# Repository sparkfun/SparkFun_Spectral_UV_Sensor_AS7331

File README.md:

SparkFun Spectral UV Sensor - AS7331 (Qwiic) 
========================================

<table class="table table-hover table-striped table-bordered">
    <tr align="center">
        <td></td>
        <td></td>
    </tr>
    <tr align="center">
        <td><a href="https://www.sparkfun.com/products/23517">SparkFun Spectral UV Sensor - AS7331 (Qwiic)</a></td>
        <td><a href="https://www.sparkfun.com/products/23518">SparkFun Mini Spectral UV Sensor - AS7331 (Qwiic)</a></td>
    </tr>
</table>

The SparkFun Spectral UV Sensor - AS7331 (Qwiic) features the AS7331 UV sensor from ams OSRAM<sup>&copy;</sup> and measures UV radiation on three channels: UVA (320-400nm), UVB (280-320nm), and UVC (200-280nm) with high sensitivity and accuracy. The three channels on the AS7331 each have individual photodiodes with built-in interference filters. The sensor has three operating modes: Single Measurement (CMD), Continuous Measurement (CONT), and Synchronized Measurement (SYNx) with an automatic power down sequence between measurements for low current consumption in all three modes. 

Repository Contents
-------------------

* **/Documentation** - Data sheets, additional product information
* **/Hardware** - Eagle design files (.brd, .sch)
* **/Production** - Production panel files (.brd)
* **/docs** -  Documentation files for the Spectral UV Sensor
* **/overrides** -  Overrides for GitHub pages content

Documentation
--------------
* **[Library](https://github.com/sparkfun/SparkFun_AS7331_Arduino_Library)** - Arduino library for the Spectral UV Sensor - AS7331 (Qwiic).
* **[Hookup Guide](https://sparkfun.github.io/SparkFun_Spectral_UV_Sensor_AS7331)** - Basic hookup guide for the Spectral UV Sensor - AS7331 (Qwiic).

Product Versions
----------------
* [SEN-23517](https://www.sparkfun.com/products/23517) - Spectral UV Sensor - AS7331 (Qwiic)
* [SEN-23518](https://www.sparkfun.com/products/23518) - Mini Spectral UV Sensor - AS7331 (Qwiic)

License Information
-------------------

This product is _**open source**_! 

Please review the LICENSE.md file for license information. 

If you have any questions or concerns on licensing, please contact technical support on our [SparkFun forums](https://forum.sparkfun.com/viewforum.php?f=152).

Distributed as-is; no warranty is given.

- Your friends at SparkFun.

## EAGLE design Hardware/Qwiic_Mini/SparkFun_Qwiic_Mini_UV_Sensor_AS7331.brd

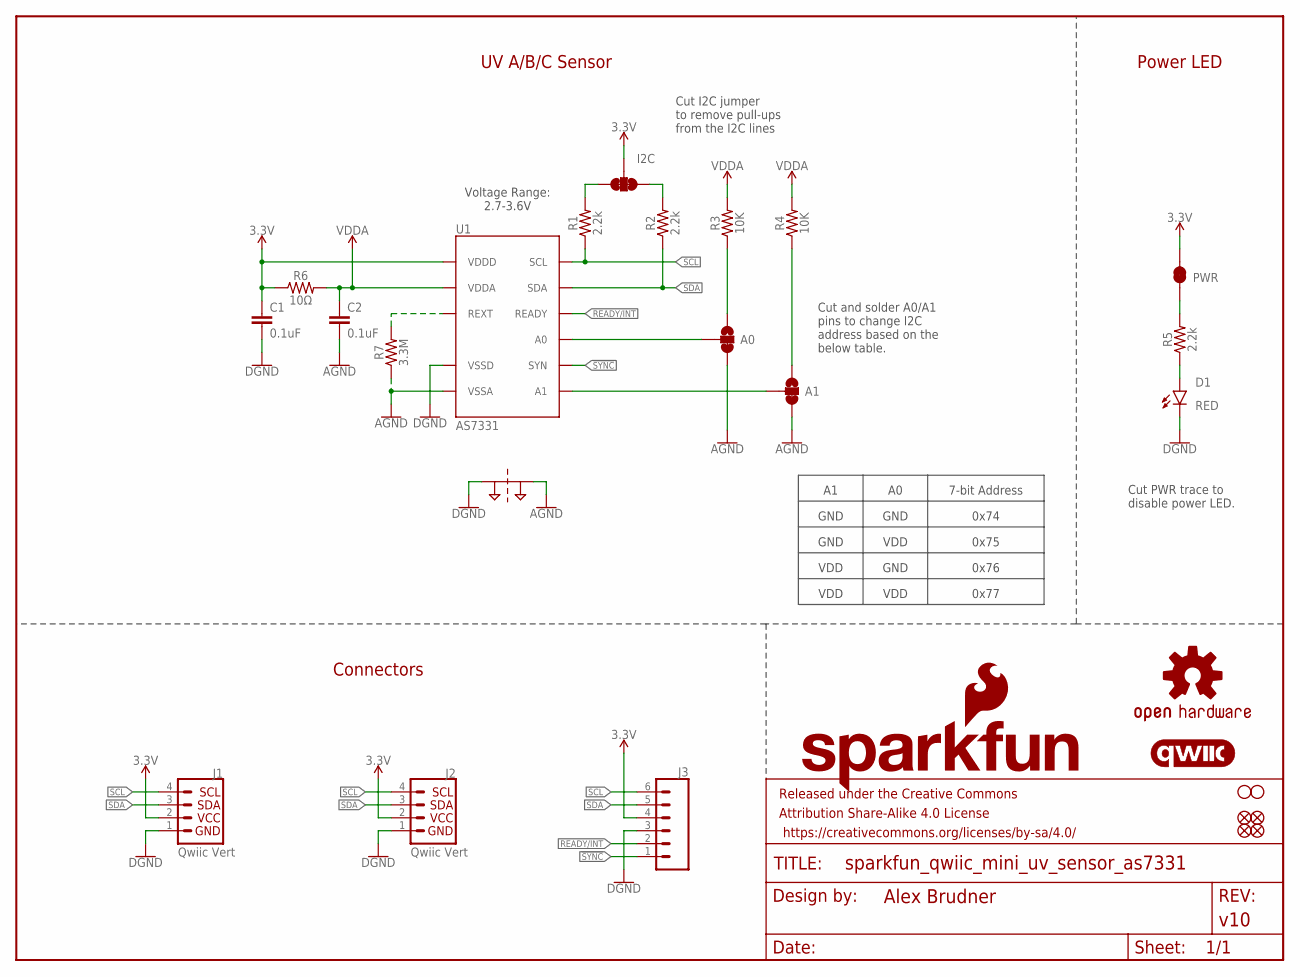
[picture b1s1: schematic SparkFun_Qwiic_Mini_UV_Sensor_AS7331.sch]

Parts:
A0, A1: JUMPER-SMT_3_1-NC_TRACE_SILK; SMT-JUMPER_3_1-NC_TRACE_SILK
C1, C2: 0.1uF; 0402-TIGHT
D1: RED; LED-0402
FD1, FD2, FD3, FD4: FIDUCIALUFIDUCIAL; FIDUCIAL-MICRO
FRAME1: FRAME-LETTER; CREATIVE_COMMONS
H1, H2: STAND-OFFTIGHT; STAND-OFF-TIGHT
I2C: JUMPER-SMT_3_2-NC_TRACE_SILK; SMT-JUMPER_3_2-NC_TRACE_SILK
J1, J2: Qwiic Vert; JST04_1MM_VERT
J3: CONN_06NO_SILK_NO_POP; 1X06_NO_SILK
LOGO1: SFE_LOGO_NAME.1_INCH; SFE_LOGO_NAME_.1
LOGO2: QWIIC_LOGO_CONNECTOR; QWIIC_5.5MM
LOGO3: OSHW-LOGOMINI; OSHW-LOGO-MINI
LOGO4: SFE_LOGO_FLAME.1_INCH; SFE_LOGO_FLAME_.1
PWR: JUMPER-SMT_2_NC_TRACE_SILK; SMT-JUMPER_2_NC_TRACE_SILK
R1, R2, R5: 2.2k; 0402-TIGHT
R3, R4: 10K; 0402-TIGHT
R6: 10Ω; 0402-TIGHT
R7: 3.3M; 1206
SUPPLYTIE1: 2PT_GND_TIE
U1: AS7331; OLGA16

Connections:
3.3V: C1.1, I2C.2, J1.2, J2.2, J3.4, PWR.2, R6.1, U1.10 (VDDD)
!SYNC: J3.1, U1.8 (SYN)
A0: A0.2, U1.14 (A0)
A1: A1.2, U1.7 (A1)
AGND: A0.3, A1.3, C2.2, R7.1, SUPPLYTIE1.P$2, U1.1 (VSSA), U1.2 (VSSA), U1.5 (VSSA), U1.6 (VSSA), U1.15 (VSSA), U1.16 (VSSA)
GND: C1.2, D1.C, J1.1, J2.1, J3.3, SUPPLYTIE1.P$1, U1.11 (VSSD)
unnamed: A0.1, R3.1
unnamed: A1.1, R4.1
unnamed: I2C.3, R1.2
unnamed: I2C.1, R2.2
unnamed: PWR.1, R5.2
unnamed: R7.2, U1.4 (REXT)
unnamed: D1.A, R5.1
READY/INT: J3.2, U1.9 (READY)
SCL: J1.4, J2.4, J3.6, R1.1, U1.13 (SCL)
SDA: J1.3, J2.3, J3.5, R2.1, U1.12 (SDA)
VDDA: C2.1, R3.2, R4.2, R6.2, U1.3 (VDDA)

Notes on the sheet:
Cut PWR trace to disable power LED.
Cut and solder A0/A1 pins to change I2C address based on the below table.
7-bit Address
GND
VDD
0x74
0x75
0x76
0x77
Connectors
UV A/B/C Sensor
Power LED
Cut I2C jumper to remove pull-ups from the I2C lines
Voltage Range: 2.7-3.6V

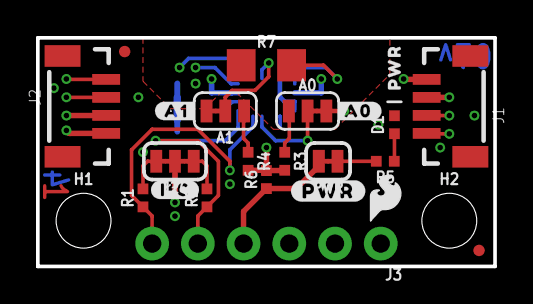
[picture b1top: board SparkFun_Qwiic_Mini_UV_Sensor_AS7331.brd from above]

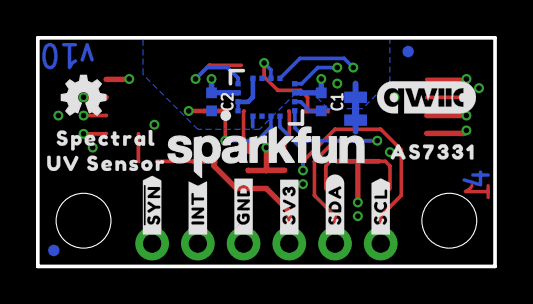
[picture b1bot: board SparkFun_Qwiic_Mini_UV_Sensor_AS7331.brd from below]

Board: 4 copper layers, 25.4 x 12.7 mm, 45 parts (18 on the bottom side), 17 nets.

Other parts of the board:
U$6: #I�C#0
U$7: #A0#0
U$8: #A1#0
U$9: #PWR#0
U$10: PWR0
U$11: #_SCL#0
U$12: #_SDA#0
U$13: #_3V3#0
U$14: #_GND#0
U$15: #_INT#0
U$17: UV_SENSOR0
U$18: AS73310
U$19: ORDERING_INSTRUCTIONS
U$20: SPECTRAL0
U$21: #_#SYN##0

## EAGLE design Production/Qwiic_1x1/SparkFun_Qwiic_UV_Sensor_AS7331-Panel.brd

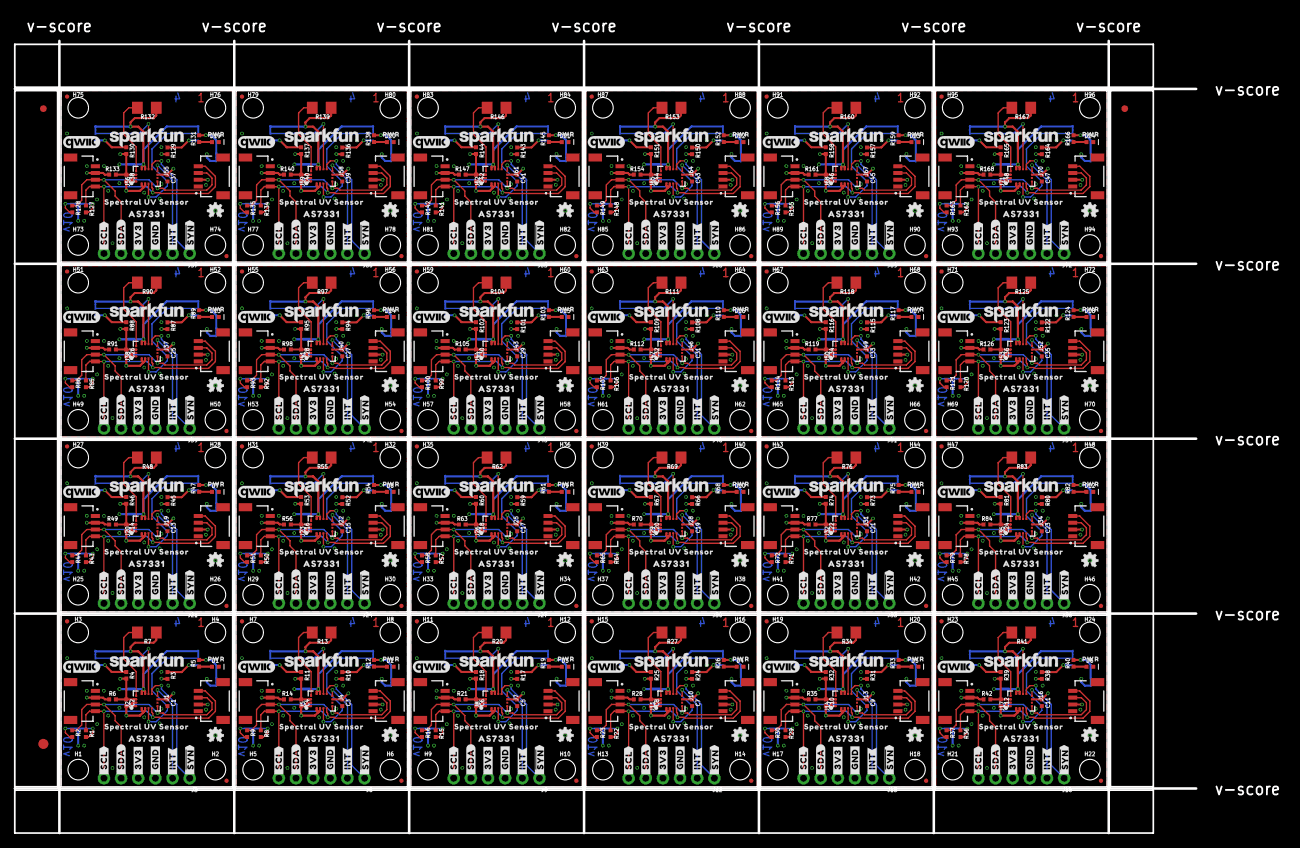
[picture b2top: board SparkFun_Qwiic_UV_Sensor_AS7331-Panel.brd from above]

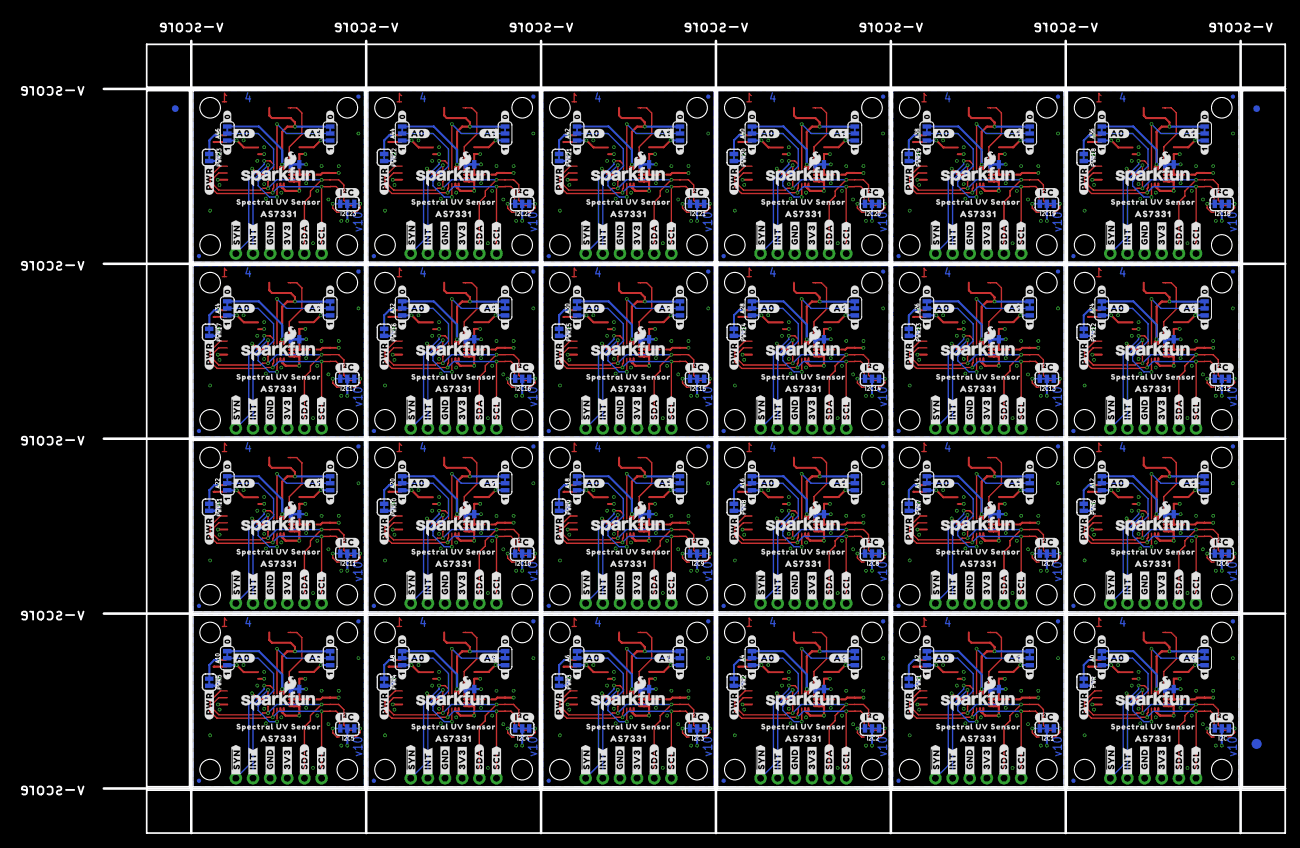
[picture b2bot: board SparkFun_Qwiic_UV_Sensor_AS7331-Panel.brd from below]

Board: 4 copper layers, 175.0 x 117.3 mm, 1374 parts (579 on the bottom side), 408 nets.

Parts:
A0, A1, A2, A3, A4, A5, A6, A7, A8, A9, A10, A11, A12, A13, A14, A15, A16, A17, A18, A19, A20, A21, A22, A23, A24, A25, A26, A27, A28, A29, A30, A31, A32, A33, A34, A35, A36, A37, A38, A39, A40, A41, A42, A43, A44, A45, A46, A47: JUMPER-SMT_3_1-NC_TRACE_SILK; SMT-JUMPER_3_1-NC_TRACE_SILK
C1, C2, C3, C4, C5, C6, C7, C8, C9, C10, C11, C12, C13, C14, C15, C16, C17, C18, C19, C20, C21, C22, C23, C24, C25, C26, C27, C28, C29, C30, C31, C32, C33, C34, C35, C36, C37, C38, C39, C40, C41, C42, C43, C44, C45, C46, C47, C48: 0.1uF; 0402-TIGHT
D1, D2, D3, D4, D5, D6, D7, D8, D9, D10, D11, D12, D13, D14, D15, D16, D17, D18, D19, D20, D21, D22, D23, D24: RED; LED-0402
E$1, E$2, E$3, E$4: FIDUCIAL-1X2
E$5, E$6: FIDUCIAL-1.5X3
FD1, FD2, FD3, FD4, FD5, FD6, FD7, FD8, FD9, FD10, FD11, FD12, FD13, FD14, FD15, FD16, FD17, FD18, FD19, FD20, FD21, FD22, FD23, FD24, FD25, FD26, FD27, FD28, FD29, FD30, FD31, FD32, FD33, FD34, FD35, FD36, FD37, FD38, FD39, FD40, FD41, FD42, FD43, FD44, FD45, FD46, FD47, FD48, FD49, FD50, FD51, FD52, FD53, FD54, FD55, FD56, FD57, FD58, FD59, FD60, FD61, FD62, FD63, FD64, FD65, FD66, FD67, FD68, FD69, FD70, FD71, FD72, FD73, FD74, FD75, FD76, FD77, FD78, FD79, FD80, FD81, FD82, FD83, FD84, FD85, FD86, FD87, FD88, FD89, FD90, FD91, FD92, FD93, FD94, FD95, FD96: FIDUCIALUFIDUCIAL; FIDUCIAL-MICRO
H1, H2, H3, H4, H5, H6, H7, H8, H9, H10, H11, H12, H13, H14, H15, H16, H17, H18, H19, H20, H21, H22, H23, H24, H25, H26, H27, H28, H29, H30, H31, H32, H33, H34, H35, H36, H37, H38, H39, H40, H41, H42, H43, H44, H45, H46, H47, H48, H49, H50, H51, H52, H53, H54, H55, H56, H57, H58, H59, H60, H61, H62, H63, H64, H65, H66, H67, H68, H69, H70, H71, H72, H73, H74, H75, H76, H77, H78, H79, H80, H81, H82, H83, H84, H85, H86, H87, H88, H89, H90, H91, H92, H93, H94, H95, H96: STAND-OFFTIGHT; STAND-OFF-TIGHT
I2C, I2C1, I2C2, I2C3, I2C4, I2C5, I2C6, I2C7, I2C8, I2C9, I2C10, I2C11, I2C12, I2C13, I2C14, I2C15, I2C16, I2C17, I2C18, I2C19, I2C20, I2C21, I2C22, I2C23: JUMPER-SMT_3_2-NC_TRACE_SILK; SMT-JUMPER_3_2-NC_TRACE_SILK
J1, J2, J4, J5, J7, J8, J10, J11, J13, J14, J16, J17, J19, J20, J22, J23, J25, J26, J28, J29, J31, J32, J34, J35, J37, J38, J40, J41, J43, J44, J46, J47, J49, J50, J52, J53, J55, J56, J58, J59, J61, J62, J64, J65, J67, J68, J70, J71: QWIIC_RA; JST04_1MM_RA
J3, J6, J9, J12, J15, J18, J21, J24, J27, J30, J33, J36, J39, J42, J45, J48, J51, J54, J57, J60, J63, J66, J69, J72: 1X06_NO_SILK
LOGO1, LOGO4, LOGO7, LOGO10, LOGO13, LOGO16, LOGO19, LOGO22, LOGO25, LOGO28, LOGO31, LOGO34, LOGO37, LOGO40, LOGO43, LOGO46, LOGO49, LOGO52, LOGO55, LOGO58, LOGO61, LOGO64, LOGO67, LOGO70: SFE_LOGO_NAME_FLAME.1_INCH; SFE_LOGO_NAME_FLAME_.1
LOGO2, LOGO5, LOGO8, LOGO11, LOGO14, LOGO17, LOGO20, LOGO23, LOGO26, LOGO29, LOGO32, LOGO35, LOGO38, LOGO41, LOGO44, LOGO47, LOGO50, LOGO53, LOGO56, LOGO59, LOGO62, LOGO65, LOGO68, LOGO71: QWIIC_LOGO_CONNECTOR; QWIIC_5.5MM
LOGO3, LOGO6, LOGO9, LOGO12, LOGO15, LOGO18, LOGO21, LOGO24, LOGO27, LOGO30, LOGO33, LOGO36, LOGO39, LOGO42, LOGO45, LOGO48, LOGO51, LOGO54, LOGO57, LOGO60, LOGO63, LOGO66, LOGO69, LOGO72: OSHW-LOGOMINI; OSHW-LOGO-MINI
PWR, PWR1, PWR2, PWR3, PWR4, PWR5, PWR6, PWR7, PWR8, PWR9, PWR10, PWR11, PWR12, PWR13, PWR14, PWR15, PWR16, PWR17, PWR18, PWR19, PWR20, PWR21, PWR22, PWR23: JUMPER-SMT_2_NC_TRACE_SILK; SMT-JUMPER_2_NC_TRACE_SILK
R1, R2, R5, R8, R9, R12, R15, R16, R19, R22, R23, R26, R29, R30, R33, R36, R37, R40, R43, R44, R47, R50, R51, R54, R57, R58, R61, R64, R65, R68, R71, R72, R75, R78, R79, R82, R85, R86, R89, R92, R93, R96, R99, R100, R103, R106, R107, R110, R113, R114, R117, R120, R121, R124, R127, R128, R131, R134, R135, R138, R141, R142, R145, R148, R149, R152, R155, R156, R159, R162, R163, R166: 2.2k; 0402-TIGHT
R3, R4, R10, R11, R17, R18, R24, R25, R31, R32, R38, R39, R45, R46, R52, R53, R59, R60, R66, R67, R73, R74, R80, R81, R87, R88, R94, R95, R101, R102, R108, R109, R115, R116, R122, R123, R129, R130, R136, R137, R143, R144, R150, R151, R157, R158, R164, R165: 10K; 0402-TIGHT
R6, R14, R21, R28, R35, R42, R49, R56, R63, R70, R77, R84, R91, R98, R105, R112, R119, R126, R133, R140, R147, R154, R161, R168: 10Ω; 0402-TIGHT
R7, R13, R20, R27, R34, R41, R48, R55, R62, R69, R76, R83, R90, R97, R104, R111, R118, R125, R132, R139, R146, R153, R160, R167: 3.3M; 1206
SUPPLYTIE1, SUPPLYTIE2, SUPPLYTIE3, SUPPLYTIE4, SUPPLYTIE5, SUPPLYTIE6, SUPPLYTIE7, SUPPLYTIE8, SUPPLYTIE9, SUPPLYTIE10, SUPPLYTIE11, SUPPLYTIE12, SUPPLYTIE13, SUPPLYTIE14, SUPPLYTIE15, SUPPLYTIE16, SUPPLYTIE17, SUPPLYTIE18, SUPPLYTIE19, SUPPLYTIE20, SUPPLYTIE21, SUPPLYTIE22, SUPPLYTIE23, SUPPLYTIE24: 2PT_GND_TIE
U1, U2, U3, U4, U5, U6, U7, U8, U9, U10, U11, U12, U13, U14, U15, U16, U17, U18, U19, U20, U21, U22, U23, U24: AS7331; OLGA16
U$1, U$10, U$55, U$82, U$109, U$136, U$163, U$190, U$217, U$244, U$271, U$298, U$325, U$352, U$379, U$406, U$433, U$460, U$487, U$514, U$541, U$568, U$595, U$622: PWR0
U$2, U$11, U$17, U$34, U$56, U$61, U$83, U$88, U$110, U$115, U$137, U$142, U$164, U$169, U$191, U$196, U$218, U$223, U$245, U$250, U$272, U$277, U$299, U$304, U$326, U$331, U$353, U$358, U$380, U$385, U$407, U$412, U$434, U$439, U$461, U$466, U$488, U$493, U$515, U$520, U$542, U$547, U$569, U$574, U$596, U$601, U$623, U$628: #_SCL#0
U$3, U$12, U$18, U$35, U$57, U$62, U$84, U$89, U$111, U$116, U$138, U$143, U$165, U$170, U$192, U$197, U$219, U$224, U$246, U$251, U$273, U$278, U$300, U$305, U$327, U$332, U$354, U$359, U$381, U$386, U$408, U$413, U$435, U$440, U$462, U$467, U$489, U$494, U$516, U$521, U$543, U$548, U$570, U$575, U$597, U$602, U$624, U$629: #_SDA#0
U$4, U$13, U$19, U$36, U$58, U$63, U$85, U$90, U$112, U$117, U$139, U$144, U$166, U$171, U$193, U$198, U$220, U$225, U$247, U$252, U$274, U$279, U$301, U$306, U$328, U$333, U$355, U$360, U$382, U$387, U$409, U$414, U$436, U$441, U$463, U$468, U$490, U$495, U$517, U$522, U$544, U$549, U$571, U$576, U$598, U$603, U$625, U$630: #_3V3#0
U$5, U$14, U$20, U$37, U$59, U$64, U$86, U$91, U$113, U$118, U$140, U$145, U$167, U$172, U$194, U$199, U$221, U$226, U$248, U$253, U$275, U$280, U$302, U$307, U$329, U$334, U$356, U$361, U$383, U$388, U$410, U$415, U$437, U$442, U$464, U$469, U$491, U$496, U$518, U$523, U$545, U$550, U$572, U$577, U$599, U$604, U$626, U$631: #_GND#0
U$6, U$39, U$66, U$93, U$120, U$147, U$174, U$201, U$228, U$255, U$282, U$309, U$336, U$363, U$390, U$417, U$444, U$471, U$498, U$525, U$552, U$579, U$606, U$633: #PWR#0
U$7, U$40, U$67, U$94, U$121, U$148, U$175, U$202, U$229, U$256, U$283, U$310, U$337, U$364, U$391, U$418, U$445, U$472, U$499, U$526, U$553, U$580, U$607, U$634: SFE_LOGO_FLAME_STOP_.1
U$8, U$29, U$44, U$49, U$71, U$76, U$98, U$103, U$125, U$130, U$152, U$157, U$179, U$184, U$206, U$211, U$233, U$238, U$260, U$265, U$287, U$292, U$314, U$319, U$341, U$346, U$368, U$373, U$395, U$400, U$422, U$427, U$449, U$454, U$476, U$481, U$503, U$508, U$530, U$535, U$557, U$562, U$584, U$589, U$611, U$616, U$638, U$643: SPECTRAL_UV_SENSOR0
U$9, U$43, U$70, U$97, U$124, U$151, U$178, U$205, U$232, U$259, U$286, U$313, U$340, U$367, U$394, U$421, U$448, U$475, U$502, U$529, U$556, U$583, U$610, U$637: #A0#0
U$15, U$21, U$23, U$38, U$60, U$65, U$87, U$92, U$114, U$119, U$141, U$146, U$168, U$173, U$195, U$200, U$222, U$227, U$249, U$254, U$276, U$281, U$303, U$308, U$330, U$335, U$357, U$362, U$384, U$389, U$411, U$416, U$438, U$443, U$465, U$470, U$492, U$497, U$519, U$524, U$546, U$551, U$573, U$578, U$600, U$605, U$627, U$632: #_INT#0
U$16, U$27, U$45, U$46, U$72, U$73, U$99, U$100, U$126, U$127, U$153, U$154, U$180, U$181, U$207, U$208, U$234, U$235, U$261, U$262, U$288, U$289, U$315, U$316, U$342, U$343, U$369, U$370, U$396, U$397, U$423, U$424, U$450, U$451, U$477, U$478, U$504, U$505, U$531, U$532, U$558, U$559, U$585, U$586, U$612, U$613, U$639, U$640: #_#SYN##0
U$22, U$47, U$74, U$101, U$128, U$155, U$182, U$209, U$236, U$263, U$290, U$317, U$344, U$371, U$398, U$425, U$452, U$479, U$506, U$533, U$560, U$587, U$614, U$641: SFE_LOGO_NAME_.1
U$24, U$50, U$77, U$104, U$131, U$158, U$185, U$212, U$239, U$266, U$293, U$320, U$347, U$374, U$401, U$428, U$455, U$482, U$509, U$536, U$563, U$590, U$617, U$644: #A1#0
U$25, U$28, U$41, U$48, U$68, U$75, U$95, U$102, U$122, U$129, U$149, U$156, U$176, U$183, U$203, U$210, U$230, U$237, U$257, U$264, U$284, U$291, U$311, U$318, U$338, U$345, U$365, U$372, U$392, U$399, U$419, U$426, U$446, U$453, U$473, U$480, U$500, U$507, U$527, U$534, U$554, U$561, U$581, U$588, U$608, U$615, U$635, U$642: AS73310
U$26, U$42, U$69, U$96, U$123, U$150, U$177, U$204, U$231, U$258, U$285, U$312, U$339, U$366, U$393, U$420, U$447, U$474, U$501, U$528, U$555, U$582, U$609, U$636: #I�C#0
U$30, U$31, U$51, U$52, U$78, U$79, U$105, U$106, U$132, U$133, U$159, U$160, U$186, U$187, U$213, U$214, U$240, U$241, U$267, U$268, U$294, U$295, U$321, U$322, U$348, U$349, U$375, U$376, U$402, U$403, U$429, U$430, U$456, U$457, U$483, U$484, U$510, U$511, U$537, U$538, U$564, U$565, U$591, U$592, U$618, U$619, U$645, U$646: #0#0
U$32, U$33, U$53, U$54, U$80, U$81, U$107, U$108, U$134, U$135, U$161, U$162, U$188, U$189, U$215, U$216, U$242, U$243, U$269, U$270, U$296, U$297, U$323, U$324, U$350, U$351, U$377, U$378, U$404, U$405, U$431, U$432, U$458, U$459, U$485, U$486, U$512, U$513, U$539, U$540, U$566, U$567, U$593, U$594, U$620, U$621, U$647, U$648: #1#0

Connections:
3.3V: C1.1, I2C.2, J1.2, J2.2, J3.4, PWR.2, R6.1, U1.10
3.3V1: C3.1, I2C1.2, J4.2, J5.2, J6.4, PWR1.2, R14.1, U2.10
3.3V2: C5.1, I2C2.2, J7.2, J8.2, J9.4, PWR2.2, R21.1, U3.10
3.3V3: C7.1, I2C3.2, J10.2, J11.2, J12.4, PWR3.2, R28.1, U4.10
3.3V4: C9.1, I2C4.2, J13.2, J14.2, J15.4, PWR4.2, R35.1, U5.10
3.3V5: C11.1, I2C5.2, J16.2, J17.2, J18.4, PWR5.2, R42.1, U6.10
3.3V6: C13.1, I2C6.2, J19.2, J20.2, J21.4, PWR6.2, R49.1, U7.10
3.3V7: C15.1, I2C7.2, J22.2, J23.2, J24.4, PWR7.2, R56.1, U8.10
3.3V8: C17.1, I2C8.2, J25.2, J26.2, J27.4, PWR8.2, R63.1, U9.10
3.3V9: C19.1, I2C9.2, J28.2, J29.2, J30.4, PWR9.2, R70.1, U10.10
3.3V10: C21.1, I2C10.2, J31.2, J32.2, J33.4, PWR10.2, R77.1, U11.10
3.3V11: C23.1, I2C11.2, J34.2, J35.2, J36.4, PWR11.2, R84.1, U12.10
3.3V12: C25.1, I2C12.2, J37.2, J38.2, J39.4, PWR12.2, R91.1, U13.10
3.3V13: C27.1, I2C13.2, J40.2, J41.2, J42.4, PWR13.2, R98.1, U14.10
3.3V14: C29.1, I2C14.2, J43.2, J44.2, J45.4, PWR14.2, R105.1, U15.10
3.3V15: C31.1, I2C15.2, J46.2, J47.2, J48.4, PWR15.2, R112.1, U16.10
3.3V16: C33.1, I2C16.2, J49.2, J50.2, J51.4, PWR16.2, R119.1, U17.10
3.3V17: C35.1, I2C17.2, J52.2, J53.2, J54.4, PWR17.2, R126.1, U18.10
3.3V18: C37.1, I2C18.2, J55.2, J56.2, J57.4, PWR18.2, R133.1, U19.10
3.3V19: C39.1, I2C19.2, J58.2, J59.2, J60.4, PWR19.2, R140.1, U20.10
3.3V20: C41.1, I2C20.2, J61.2, J62.2, J63.4, PWR20.2, R147.1, U21.10
3.3V21: C43.1, I2C21.2, J64.2, J65.2, J66.4, PWR21.2, R154.1, U22.10
3.3V22: C45.1, I2C22.2, J67.2, J68.2, J69.4, PWR22.2, R161.1, U23.10
3.3V23: C47.1, I2C23.2, J70.2, J71.2, J72.4, PWR23.2, R168.1, U24.10
A0: A0.2, U1.14
A1: A1.2, U1.7
A2: A2.2, U2.14
A3: A3.2, U2.7
A4: A4.2, U3.14
A5: A5.2, U3.7
A6: A6.2, U4.14
A7: A7.2, U4.7
A8: A8.2, U5.14
A9: A9.2, U5.7
A10: A10.2, U6.14
A11: A11.2, U6.7
A12: A12.2, U7.14
A13: A13.2, U7.7
A14: A14.2, U8.14
A15: A15.2, U8.7
A16: A16.2, U9.14
A17: A17.2, U9.7
A18: A18.2, U10.14
A19: A19.2, U10.7
A20: A20.2, U11.14
A21: A21.2, U11.7
A22: A22.2, U12.14
A23: A23.2, U12.7
A24: A24.2, U13.14
A25: A25.2, U13.7
A26: A26.2, U14.14
A27: A27.2, U14.7
A28: A28.2, U15.14
A29: A29.2, U15.7
A30: A30.2, U16.14
A31: A31.2, U16.7
A32: A32.2, U17.14
A33: A33.2, U17.7
A34: A34.2, U18.14
A35: A35.2, U18.7
A36: A36.2, U19.14
A37: A37.2, U19.7
A38: A38.2, U20.14
A39: A39.2, U20.7
A40: A40.2, U21.14
A41: A41.2, U21.7
A42: A42.2, U22.14
A43: A43.2, U22.7
A44: A44.2, U23.14
A45: A45.2, U23.7
A46: A46.2, U24.14
A47: A47.2, U24.7
AGND: A0.3, A1.3, C2.2, R7.1, SUPPLYTIE1.P$2, U1.1, U1.2, U1.5, U1.6, U1.15, U1.16
AGND1: A2.3, A3.3, C4.2, R13.1, SUPPLYTIE2.P$2, U2.1, U2.2, U2.5, U2.6, U2.15, U2.16
AGND2: A4.3, A5.3, C6.2, R20.1, SUPPLYTIE3.P$2, U3.1, U3.2, U3.5, U3.6, U3.15, U3.16
AGND3: A6.3, A7.3, C8.2, R27.1, SUPPLYTIE4.P$2, U4.1, U4.2, U4.5, U4.6, U4.15, U4.16
AGND4: A8.3, A9.3, C10.2, R34.1, SUPPLYTIE5.P$2, U5.1, U5.2, U5.5, U5.6, U5.15, U5.16
AGND5: A10.3, A11.3, C12.2, R41.1, SUPPLYTIE6.P$2, U6.1, U6.2, U6.5, U6.6, U6.15, U6.16
AGND6: A12.3, A13.3, C14.2, R48.1, SUPPLYTIE7.P$2, U7.1, U7.2, U7.5, U7.6, U7.15, U7.16
AGND7: A14.3, A15.3, C16.2, R55.1, SUPPLYTIE8.P$2, U8.1, U8.2, U8.5, U8.6, U8.15, U8.16
AGND8: A16.3, A17.3, C18.2, R62.1, SUPPLYTIE9.P$2, U9.1, U9.2, U9.5, U9.6, U9.15, U9.16
AGND9: A18.3, A19.3, C20.2, R69.1, SUPPLYTIE10.P$2, U10.1, U10.2, U10.5, U10.6, U10.15, U10.16
AGND10: A20.3, A21.3, C22.2, R76.1, SUPPLYTIE11.P$2, U11.1, U11.2, U11.5, U11.6, U11.15, U11.16
AGND11: A22.3, A23.3, C24.2, R83.1, SUPPLYTIE12.P$2, U12.1, U12.2, U12.5, U12.6, U12.15, U12.16
AGND12: A24.3, A25.3, C26.2, R90.1, SUPPLYTIE13.P$2, U13.1, U13.2, U13.5, U13.6, U13.15, U13.16
AGND13: A26.3, A27.3, C28.2, R97.1, SUPPLYTIE14.P$2, U14.1, U14.2, U14.5, U14.6, U14.15, U14.16
AGND14: A28.3, A29.3, C30.2, R104.1, SUPPLYTIE15.P$2, U15.1, U15.2, U15.5, U15.6, U15.15, U15.16
AGND15: A30.3, A31.3, C32.2, R111.1, SUPPLYTIE16.P$2, U16.1, U16.2, U16.5, U16.6, U16.15, U16.16
AGND16: A32.3, A33.3, C34.2, R118.1, SUPPLYTIE17.P$2, U17.1, U17.2, U17.5, U17.6, U17.15, U17.16
AGND17: A34.3, A35.3, C36.2, R125.1, SUPPLYTIE18.P$2, U18.1, U18.2, U18.5, U18.6, U18.15, U18.16
AGND18: A36.3, A37.3, C38.2, R132.1, SUPPLYTIE19.P$2, U19.1, U19.2, U19.5, U19.6, U19.15, U19.16
AGND19: A38.3, A39.3, C40.2, R139.1, SUPPLYTIE20.P$2, U20.1, U20.2, U20.5, U20.6, U20.15, U20.16
AGND20: A40.3, A41.3, C42.2, R146.1, SUPPLYTIE21.P$2, U21.1, U21.2, U21.5, U21.6, U21.15, U21.16
AGND21: A42.3, A43.3, C44.2, R153.1, SUPPLYTIE22.P$2, U22.1, U22.2, U22.5, U22.6, U22.15, U22.16
AGND22: A44.3, A45.3, C46.2, R160.1, SUPPLYTIE23.P$2, U23.1, U23.2, U23.5, U23.6, U23.15, U23.16
AGND23: A46.3, A47.3, C48.2, R167.1, SUPPLYTIE24.P$2, U24.1, U24.2, U24.5, U24.6, U24.15, U24.16
GND: C1.2, D1.C, J1.1, J2.1, J3.3, SUPPLYTIE1.P$1, U1.11
GND1: C3.2, D2.C, J4.1, J5.1, J6.3, SUPPLYTIE2.P$1, U2.11
GND2: C5.2, D3.C, J7.1, J8.1, J9.3, SUPPLYTIE3.P$1, U3.11
GND3: C7.2, D4.C, J10.1, J11.1, J12.3, SUPPLYTIE4.P$1, U4.11
GND4: C9.2, D5.C, J13.1, J14.1, J15.3, SUPPLYTIE5.P$1, U5.11
GND5: C11.2, D6.C, J16.1, J17.1, J18.3, SUPPLYTIE6.P$1, U6.11
GND6: C13.2, D7.C, J19.1, J20.1, J21.3, SUPPLYTIE7.P$1, U7.11
GND7: C15.2, D8.C, J22.1, J23.1, J24.3, SUPPLYTIE8.P$1, U8.11
GND8: C17.2, D9.C, J25.1, J26.1, J27.3, SUPPLYTIE9.P$1, U9.11
GND9: C19.2, D10.C, J28.1, J29.1, J30.3, SUPPLYTIE10.P$1, U10.11
GND10: C21.2, D11.C, J31.1, J32.1, J33.3, SUPPLYTIE11.P$1, U11.11
GND11: C23.2, D12.C, J34.1, J35.1, J36.3, SUPPLYTIE12.P$1, U12.11
GND12: C25.2, D13.C, J37.1, J38.1, J39.3, SUPPLYTIE13.P$1, U13.11
GND13: C27.2, D14.C, J40.1, J41.1, J42.3, SUPPLYTIE14.P$1, U14.11
GND14: C29.2, D15.C, J43.1, J44.1, J45.3, SUPPLYTIE15.P$1, U15.11
GND15: C31.2, D16.C, J46.1, J47.1, J48.3, SUPPLYTIE16.P$1, U16.11
GND16: C33.2, D17.C, J49.1, J50.1, J51.3, SUPPLYTIE17.P$1, U17.11
GND17: C35.2, D18.C, J52.1, J53.1, J54.3, SUPPLYTIE18.P$1, U18.11
GND18: C37.2, D19.C, J55.1, J56.1, J57.3, SUPPLYTIE19.P$1, U19.11
GND19: C39.2, D20.C, J58.1, J59.1, J60.3, SUPPLYTIE20.P$1, U20.11
GND20: C41.2, D21.C, J61.1, J62.1, J63.3, SUPPLYTIE21.P$1, U21.11
GND21: C43.2, D22.C, J64.1, J65.1, J66.3, SUPPLYTIE22.P$1, U22.11
GND22: C45.2, D23.C, J67.1, J68.1, J69.3, SUPPLYTIE23.P$1, U23.11
GND23: C47.2, D24.C, J70.1, J71.1, J72.3, SUPPLYTIE24.P$1, U24.11
unnamed: A0.1, R3.1
unnamed: A1.1, R4.1
unnamed: I2C.3, R1.2
unnamed: I2C1.3, R8.2
unnamed: I2C.1, R2.2
unnamed: I2C1.1, R9.2
unnamed: PWR.1, R5.2
unnamed: R7.2, U1.4
unnamed: D1.A, R5.1
unnamed: A2.1, R10.1
unnamed: A3.1, R11.1
unnamed: D2.A, R12.1
unnamed: R13.2, U2.4
unnamed: PWR1.1, R12.2
unnamed: I2C2.3, R15.2
unnamed: I2C2.1, R16.2
unnamed: A4.1, R17.1
unnamed: A5.1, R18.1
unnamed: D3.A, R19.1
unnamed: R20.2, U3.4
unnamed: PWR2.1, R19.2
unnamed: I2C3.3, R22.2
unnamed: I2C3.1, R23.2
unnamed: A6.1, R24.1
unnamed: A7.1, R25.1
unnamed: D4.A, R26.1
unnamed: R27.2, U4.4
unnamed: PWR3.1, R26.2
unnamed: I2C4.3, R29.2
unnamed: I2C4.1, R30.2
unnamed: A8.1, R31.1
unnamed: A9.1, R32.1
unnamed: D5.A, R33.1
unnamed: R34.2, U5.4
unnamed: PWR4.1, R33.2
unnamed: I2C5.3, R36.2
unnamed: I2C5.1, R37.2
unnamed: A10.1, R38.1
unnamed: A11.1, R39.1
unnamed: D6.A, R40.1
unnamed: R41.2, U6.4
unnamed: PWR5.1, R40.2
unnamed: I2C6.3, R43.2
unnamed: I2C6.1, R44.2
unnamed: A12.1, R45.1
unnamed: A13.1, R46.1
unnamed: D7.A, R47.1
unnamed: R48.2, U7.4
unnamed: PWR6.1, R47.2
unnamed: I2C7.3, R50.2
unnamed: I2C7.1, R51.2
unnamed: A14.1, R52.1
unnamed: A15.1, R53.1
unnamed: D8.A, R54.1
unnamed: R55.2, U8.4
unnamed: PWR7.1, R54.2
unnamed: I2C8.3, R57.2
unnamed: I2C8.1, R58.2
unnamed: A16.1, R59.1
unnamed: A17.1, R60.1
unnamed: D9.A, R61.1
unnamed: R62.2, U9.4
unnamed: PWR8.1, R61.2
unnamed: I2C9.3, R64.2
unnamed: I2C9.1, R65.2
unnamed: A18.1, R66.1
unnamed: A19.1, R67.1
unnamed: D10.A, R68.1
unnamed: R69.2, U10.4
unnamed: PWR9.1, R68.2
unnamed: I2C10.3, R71.2
unnamed: I2C10.1, R72.2
unnamed: A20.1, R73.1
unnamed: A21.1, R74.1
unnamed: D11.A, R75.1
unnamed: R76.2, U11.4
unnamed: PWR10.1, R75.2
unnamed: I2C11.3, R78.2
unnamed: I2C11.1, R79.2
unnamed: A22.1, R80.1
unnamed: A23.1, R81.1
unnamed: D12.A, R82.1
unnamed: R83.2, U12.4
unnamed: PWR11.1, R82.2
unnamed: I2C12.3, R85.2
unnamed: I2C12.1, R86.2
unnamed: A24.1, R87.1
unnamed: A25.1, R88.1
unnamed: D13.A, R89.1
unnamed: R90.2, U13.4
unnamed: PWR12.1, R89.2
unnamed: I2C13.3, R92.2
unnamed: I2C13.1, R93.2
unnamed: A26.1, R94.1
unnamed: A27.1, R95.1
unnamed: D14.A, R96.1
unnamed: R97.2, U14.4
unnamed: PWR13.1, R96.2
unnamed: I2C14.3, R99.2
unnamed: I2C14.1, R100.2
unnamed: A28.1, R101.1
unnamed: A29.1, R102.1
unnamed: D15.A, R103.1
unnamed: R104.2, U15.4
unnamed: PWR14.1, R103.2
unnamed: I2C15.3, R106.2
unnamed: I2C15.1, R107.2
unnamed: A30.1, R108.1
unnamed: A31.1, R109.1
unnamed: D16.A, R110.1
unnamed: R111.2, U16.4
unnamed: PWR15.1, R110.2
unnamed: I2C16.3, R113.2
unnamed: I2C16.1, R114.2
unnamed: A32.1, R115.1
unnamed: A33.1, R116.1
unnamed: D17.A, R117.1
unnamed: R118.2, U17.4
unnamed: PWR16.1, R117.2
unnamed: I2C17.3, R120.2
unnamed: I2C17.1, R121.2
unnamed: A34.1, R122.1
unnamed: A35.1, R123.1
unnamed: D18.A, R124.1
unnamed: R125.2, U18.4
unnamed: PWR17.1, R124.2
unnamed: I2C18.3, R127.2
unnamed: I2C18.1, R128.2
unnamed: A36.1, R129.1
unnamed: A37.1, R130.1
unnamed: D19.A, R131.1
unnamed: R132.2, U19.4
unnamed: PWR18.1, R131.2
unnamed: I2C19.3, R134.2
unnamed: I2C19.1, R135.2
unnamed: A38.1, R136.1
unnamed: A39.1, R137.1
unnamed: D20.A, R138.1
unnamed: R139.2, U20.4
unnamed: PWR19.1, R138.2
unnamed: I2C20.3, R141.2
unnamed: I2C20.1, R142.2
unnamed: A40.1, R143.1
unnamed: A41.1, R144.1
unnamed: D21.A, R145.1
unnamed: R146.2, U21.4
unnamed: PWR20.1, R145.2
unnamed: I2C21.3, R148.2
unnamed: I2C21.1, R149.2
unnamed: A42.1, R150.1
unnamed: A43.1, R151.1
unnamed: D22.A, R152.1
unnamed: R153.2, U22.4
unnamed: PWR21.1, R152.2
unnamed: I2C22.3, R155.2
unnamed: I2C22.1, R156.2
unnamed: A44.1, R157.1
unnamed: A45.1, R158.1
unnamed: D23.A, R159.1
unnamed: R160.2, U23.4
unnamed: PWR22.1, R159.2
unnamed: I2C23.3, R162.2
unnamed: I2C23.1, R163.2
unnamed: A46.1, R164.1
unnamed: A47.1, R165.1
unnamed: D24.A, R166.1
unnamed: R167.2, U24.4
unnamed: PWR23.1, R166.2
READY/INT: J3.2, U1.9
READY/INT1: J6.2, U2.9
READY/INT2: J9.2, U3.9
READY/INT3: J12.2, U4.9
READY/INT4: J15.2, U5.9
READY/INT5: J18.2, U6.9
READY/INT6: J21.2, U7.9
READY/INT7: J24.2, U8.9
READY/INT8: J27.2, U9.9
READY/INT9: J30.2, U10.9
READY/INT10: J33.2, U11.9
READY/INT11: J36.2, U12.9
READY/INT12: J39.2, U13.9
READY/INT13: J42.2, U14.9
READY/INT14: J45.2, U15.9
READY/INT15: J48.2, U16.9
READY/INT16: J51.2, U17.9
READY/INT17: J54.2, U18.9
READY/INT18: J57.2, U19.9
READY/INT19: J60.2, U20.9
READY/INT20: J63.2, U21.9
READY/INT21: J66.2, U22.9
READY/INT22: J69.2, U23.9
READY/INT23: J72.2, U24.9
SCL: J1.4, J2.4, J3.6, R1.1, U1.13
SCL1: J4.4, J5.4, J6.6, R8.1, U2.13
SCL2: J7.4, J8.4, J9.6, R15.1, U3.13
SCL3: J10.4, J11.4, J12.6, R22.1, U4.13
SCL4: J13.4, J14.4, J15.6, R29.1, U5.13
SCL5: J16.4, J17.4, J18.6, R36.1, U6.13
SCL6: J19.4, J20.4, J21.6, R43.1, U7.13
SCL7: J22.4, J23.4, J24.6, R50.1, U8.13
SCL8: J25.4, J26.4, J27.6, R57.1, U9.13
SCL9: J28.4, J29.4, J30.6, R64.1, U10.13
SCL10: J31.4, J32.4, J33.6, R71.1, U11.13
SCL11: J34.4, J35.4, J36.6, R78.1, U12.13
SCL12: J37.4, J38.4, J39.6, R85.1, U13.13
SCL13: J40.4, J41.4, J42.6, R92.1, U14.13
SCL14: J43.4, J44.4, J45.6, R99.1, U15.13
SCL15: J46.4, J47.4, J48.6, R106.1, U16.13
SCL16: J49.4, J50.4, J51.6, R113.1, U17.13
SCL17: J52.4, J53.4, J54.6, R120.1, U18.13
SCL18: J55.4, J56.4, J57.6, R127.1, U19.13
SCL19: J58.4, J59.4, J60.6, R134.1, U20.13
SCL20: J61.4, J62.4, J63.6, R141.1, U21.13
SCL21: J64.4, J65.4, J66.6, R148.1, U22.13
SCL22: J67.4, J68.4, J69.6, R155.1, U23.13
SCL23: J70.4, J71.4, J72.6, R162.1, U24.13
SDA: J1.3, J2.3, J3.5, R2.1, U1.12
SDA1: J4.3, J5.3, J6.5, R9.1, U2.12
SDA2: J7.3, J8.3, J9.5, R16.1, U3.12
SDA3: J10.3, J11.3, J12.5, R23.1, U4.12
SDA4: J13.3, J14.3, J15.5, R30.1, U5.12
SDA5: J16.3, J17.3, J18.5, R37.1, U6.12
SDA6: J19.3, J20.3, J21.5, R44.1, U7.12
SDA7: J22.3, J23.3, J24.5, R51.1, U8.12
SDA8: J25.3, J26.3, J27.5, R58.1, U9.12
SDA9: J28.3, J29.3, J30.5, R65.1, U10.12
SDA10: J31.3, J32.3, J33.5, R72.1, U11.12
SDA11: J34.3, J35.3, J36.5, R79.1, U12.12
SDA12: J37.3, J38.3, J39.5, R86.1, U13.12
SDA13: J40.3, J41.3, J42.5, R93.1, U14.12
SDA14: J43.3, J44.3, J45.5, R100.1, U15.12
SDA15: J46.3, J47.3, J48.5, R107.1, U16.12
SDA16: J49.3, J50.3, J51.5, R114.1, U17.12
SDA17: J52.3, J53.3, J54.5, R121.1, U18.12
SDA18: J55.3, J56.3, J57.5, R128.1, U19.12
SDA19: J58.3, J59.3, J60.5, R135.1, U20.12
SDA20: J61.3, J62.3, J63.5, R142.1, U21.12
SDA21: J64.3, J65.3, J66.5, R149.1, U22.12
SDA22: J67.3, J68.3, J69.5, R156.1, U23.12
SDA23: J70.3, J71.3, J72.5, R163.1, U24.12
SYNC: J3.1, U1.8
SYNC1: J6.1, U2.8
SYNC2: J9.1, U3.8
SYNC3: J12.1, U4.8
SYNC4: J15.1, U5.8
SYNC5: J18.1, U6.8
SYNC6: J21.1, U7.8
SYNC7: J24.1, U8.8
SYNC8: J27.1, U9.8
SYNC9: J30.1, U10.8
SYNC10: J33.1, U11.8
SYNC11: J36.1, U12.8
SYNC12: J39.1, U13.8
SYNC13: J42.1, U14.8
SYNC14: J45.1, U15.8
SYNC15: J48.1, U16.8
SYNC16: J51.1, U17.8
SYNC17: J54.1, U18.8
SYNC18: J57.1, U19.8
SYNC19: J60.1, U20.8
SYNC20: J63.1, U21.8
SYNC21: J66.1, U22.8
SYNC22: J69.1, U23.8
SYNC23: J72.1, U24.8
VDDA: C2.1, R3.2, R4.2, R6.2, U1.3
VDDA1: C4.1, R10.2, R11.2, R14.2, U2.3
VDDA2: C6.1, R17.2, R18.2, R21.2, U3.3
VDDA3: C8.1, R24.2, R25.2, R28.2, U4.3
VDDA4: C10.1, R31.2, R32.2, R35.2, U5.3
VDDA5: C12.1, R38.2, R39.2, R42.2, U6.3
VDDA6: C14.1, R45.2, R46.2, R49.2, U7.3
VDDA7: C16.1, R52.2, R53.2, R56.2, U8.3
VDDA8: C18.1, R59.2, R60.2, R63.2, U9.3
VDDA9: C20.1, R66.2, R67.2, R70.2, U10.3
VDDA10: C22.1, R73.2, R74.2, R77.2, U11.3
VDDA11: C24.1, R80.2, R81.2, R84.2, U12.3
VDDA12: C26.1, R87.2, R88.2, R91.2, U13.3
VDDA13: C28.1, R94.2, R95.2, R98.2, U14.3
VDDA14: C30.1, R101.2, R102.2, R105.2, U15.3
VDDA15: C32.1, R108.2, R109.2, R112.2, U16.3
VDDA16: C34.1, R115.2, R116.2, R119.2, U17.3
VDDA17: C36.1, R122.2, R123.2, R126.2, U18.3
VDDA18: C38.1, R129.2, R130.2, R133.2, U19.3
VDDA19: C40.1, R136.2, R137.2, R140.2, U20.3
VDDA20: C42.1, R143.2, R144.2, R147.2, U21.3
VDDA21: C44.1, R150.2, R151.2, R154.2, U22.3
VDDA22: C46.1, R157.2, R158.2, R161.2, U23.3
VDDA23: C48.1, R164.2, R165.2, R168.2, U24.3

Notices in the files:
parts and their libraries:
SparkFun-Aesthetics: Licensing: Creative Commons ShareAlike 4.0 International - https://creativecommons.org/licenses/by-sa/4.0
SparkFun-Aesthetics: Released under the Creative Commons Attribution Share-Alike 4.0 License
SparkFun-Aesthetics: https://creativecommons.org/licenses/by-sa/4.0
